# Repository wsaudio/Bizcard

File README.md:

# Bizcard
Drum machine business card: STM32F030 Based drum machine with 4 sounds and 16 pads

FOLDERS
Hardware:
	- Schematics: PDF of schematics
	- Gerbers: Gerber and drill files required for manufacturer
	- Project Files: KiCad V4.0.0 (or later) required to open
	- BOM: Bill of materials required for manufacture
Software: Created with Keil uVision 5.0

Pins configuration:
PA7: Audio output (TIM1 PWM1)
PA0, PA1, PA2, PA3, PA4: LED/Button MUX Out
PA5, PA6, PA9, PA10: LED MUX In
PA13, PA14, PF0, PF1: Button MUX In

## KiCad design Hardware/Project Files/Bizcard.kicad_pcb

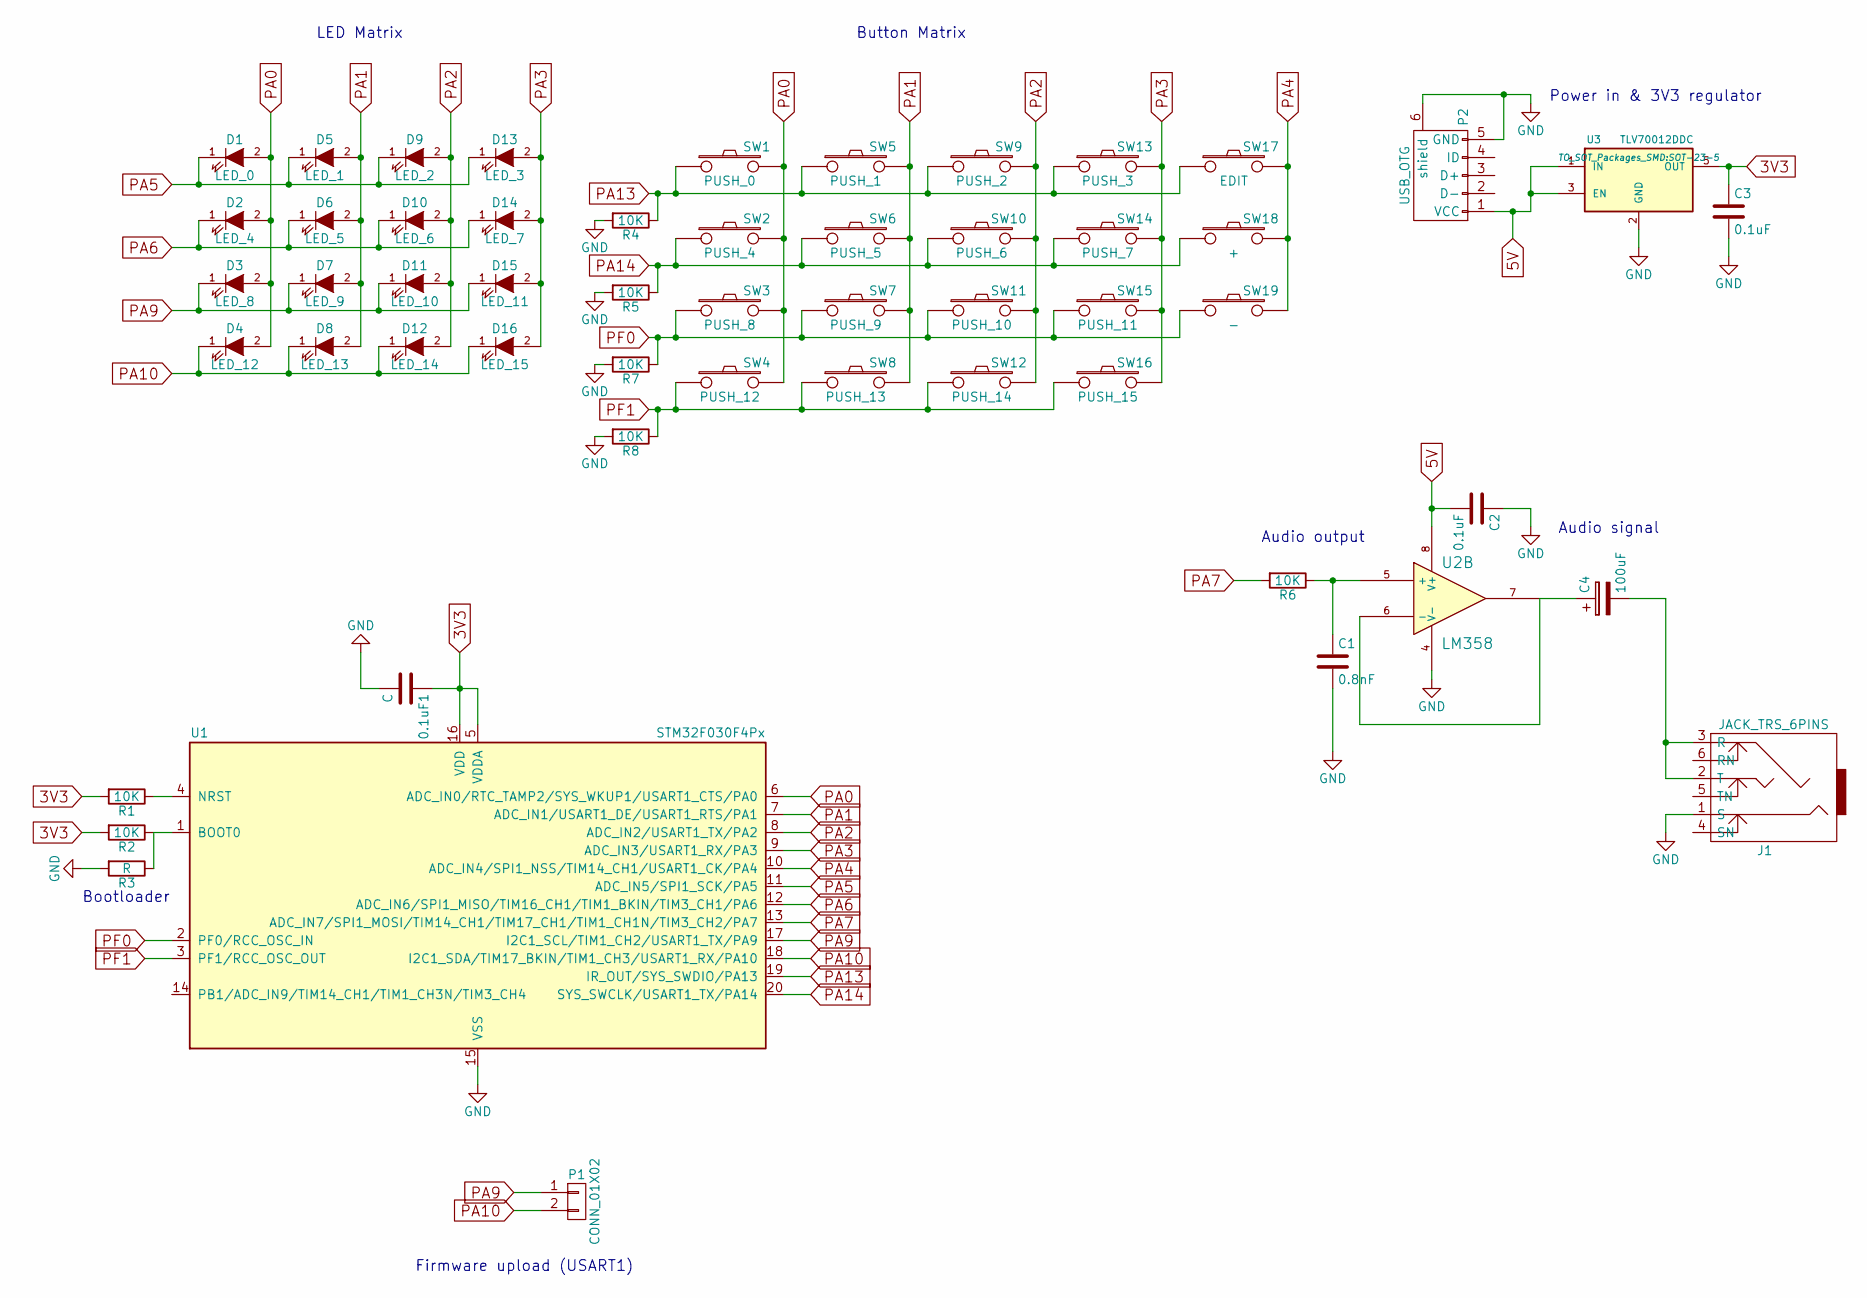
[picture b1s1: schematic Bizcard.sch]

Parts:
0.1uF1: C; C_0402
C1: 0.8nF; C_0402
C2, C3: 0.1uF; C_0402
C4: 100uF; CP_Elec_6.3x4.5
D1: LED_0; LED_0603
D2: LED_4; LED_0603
D3: LED_8; LED_0603
D4: LED_12; LED_0603
D5: LED_1; LED_0603
D6: LED_5; LED_0603
D7: LED_9; LED_0603
D8: LED_13; LED_0603
D9: LED_2; LED_0603
D10: LED_6; LED_0603
D11: LED_10; LED_0603
D12: LED_14; LED_0603
D13: LED_3; LED_0603
D14: LED_7; LED_0603
D15: LED_11; LED_0603
D16: LED_15; LED_0603
J1: JACK_TRS_6PINS; Tayda_3.5mm_stereo_TRS_jack_A-853
P1: CONN_01X02; Pin_Header_Straight_1x02_Pitch2.00mm
P2: USB_OTG; USB_Micro-B_Wuerth-629105150521
R1, R2, R4, R5, R6, R7, R8: 10K; R_0402
R3: R; R_0402
SW1: PUSH_0; SW_PUSH_6mm
SW2: PUSH_4; SW_PUSH_6mm
SW3: PUSH_8; SW_PUSH_6mm
SW4: PUSH_12; SW_PUSH_6mm
SW5: PUSH_1; SW_PUSH_6mm
SW6: PUSH_5; SW_PUSH_6mm
SW7: PUSH_9; SW_PUSH_6mm
SW8: PUSH_13; SW_PUSH_6mm
SW9: PUSH_2; SW_PUSH_6mm
SW10: PUSH_6; SW_PUSH_6mm
SW11: PUSH_10; SW_PUSH_6mm
SW12: PUSH_14; SW_PUSH_6mm
SW13: PUSH_3; SW_PUSH_6mm
SW14: PUSH_7; SW_PUSH_6mm
SW15: PUSH_11; SW_PUSH_6mm
SW16: PUSH_15; SW_PUSH_6mm
SW17: EDIT; SW_PUSH_6mm
SW18: +; SW_PUSH_6mm
SW19: -; SW_PUSH_6mm
U1: STM32F030F4Px; TSSOP-20_4.4x6.5mm_Pitch0.65mm
U2: LM358; SOIC-8_3.9x4.9mm_Pitch1.27mm
U3: TLV70012DDC; SOT-23-5

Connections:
3V3: 0.1uF1.1, C3.1, R1.2, R2.2, U1.5 (VDDA), U1.16 (VDD), U3.5 (OUT)
5V: C2.2, P2.1 (VCC), U2.8 (V+), U3.1 (IN), U3.3 (EN)
GND: 0.1uF1.2, C1.2, C2.1, C3.2, J1.1 (S), P2.5 (GND), P2.6 (shield), R3.2, R4.2, R5.2, R7.2, R8.2, U1.15 (VSS), U2.4 (V-), U3.2 (GND)
unnamed: C1.1, R6.1, U2.5 (+)
unnamed: C4.1, U2.6 (-), U2.7
unnamed: C4.2, J1.2 (T), J1.3 (R)
unnamed: R1.1, U1.4 (NRST)
unnamed: R2.1, R3.1, U1.1 (BOOT0)
PA0: D1.2 (A), D2.2 (A), D3.2 (A), D4.2 (A), SW1.2, SW2.2, SW3.2, SW4.2, U1.6 (ADC_IN0/RTC_TAMP2/SYS_WKUP1/USART1_CTS/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)
PA1: D5.2 (A), D6.2 (A), D7.2 (A), D8.2 (A), SW5.2, SW6.2, SW7.2, SW8.2, U1.7 (ADC_IN1/USART1_DE/USART1_RTS/PA1)
PA2: D9.2 (A), D10.2 (A), D11.2 (A), D12.2 (A), SW9.2, SW10.2, SW11.2, SW12.2, U1.8 (ADC_IN2/USART1_TX/PA2)
PA3: D13.2 (A), D14.2 (A), D15.2 (A), D16.2 (A), SW13.2, SW14.2, SW15.2, SW16.2, U1.9 (ADC_IN3/USART1_RX/PA3)
PA4: SW17.2, SW18.2, SW19.2, U1.10 (ADC_IN4/SPI1_NSS/TIM14_CH1/USART1_CK/PA4)
PA5: D1.1 (K), D5.1 (K), D9.1 (K), D13.1 (K), U1.11 (ADC_IN5/SPI1_SCK/PA5)
PA6: D2.1 (K), D6.1 (K), D10.1 (K), D14.1 (K), U1.12 (ADC_IN6/SPI1_MISO/TIM16_CH1/TIM1_BKIN/T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)
PA7: R6.2, U1.13 (ADC_IN7/SPI1_MOSI/TIM14_CH1/TIM17_CH1/T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)
PA9: D3.1 (K), D7.1 (K), D11.1 (K), D15.1 (K), P1.1, U1.17 (I2C1_SCL/TIM1_CH2/USART1_TX/PA9)
PA10: D4.1 (K), D8.1 (K), D12.1 (K), D16.1 (K), P1.2, U1.18 (I2C1_SDA/TIM17_BKIN/TIM1_CH3/USART1_RX/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)
PA13: R4.1, SW1.1, SW5.1, SW9.1, SW13.1, SW17.1, U1.19 (IR_OUT/SYS_SWDIO/PA13)
PA14: R5.1, SW2.1, SW6.1, SW10.1, SW14.1, SW18.1, U1.20 (SYS_SWCLK/USART1_TX/PA14)
PF0: R7.1, SW3.1, SW7.1, SW11.1, SW15.1, SW19.1, U1.2 (PF0/RCC_OSC_IN)
PF1: R8.1, SW4.1, SW8.1, SW12.1, SW16.1, U1.3 (PF1/RCC_OSC_OUT)

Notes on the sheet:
Firmware upload (USART1)
LED Matrix
Button Matrix
Power in & 3V3 regulator
Audio output
Audio signal
Bootloader

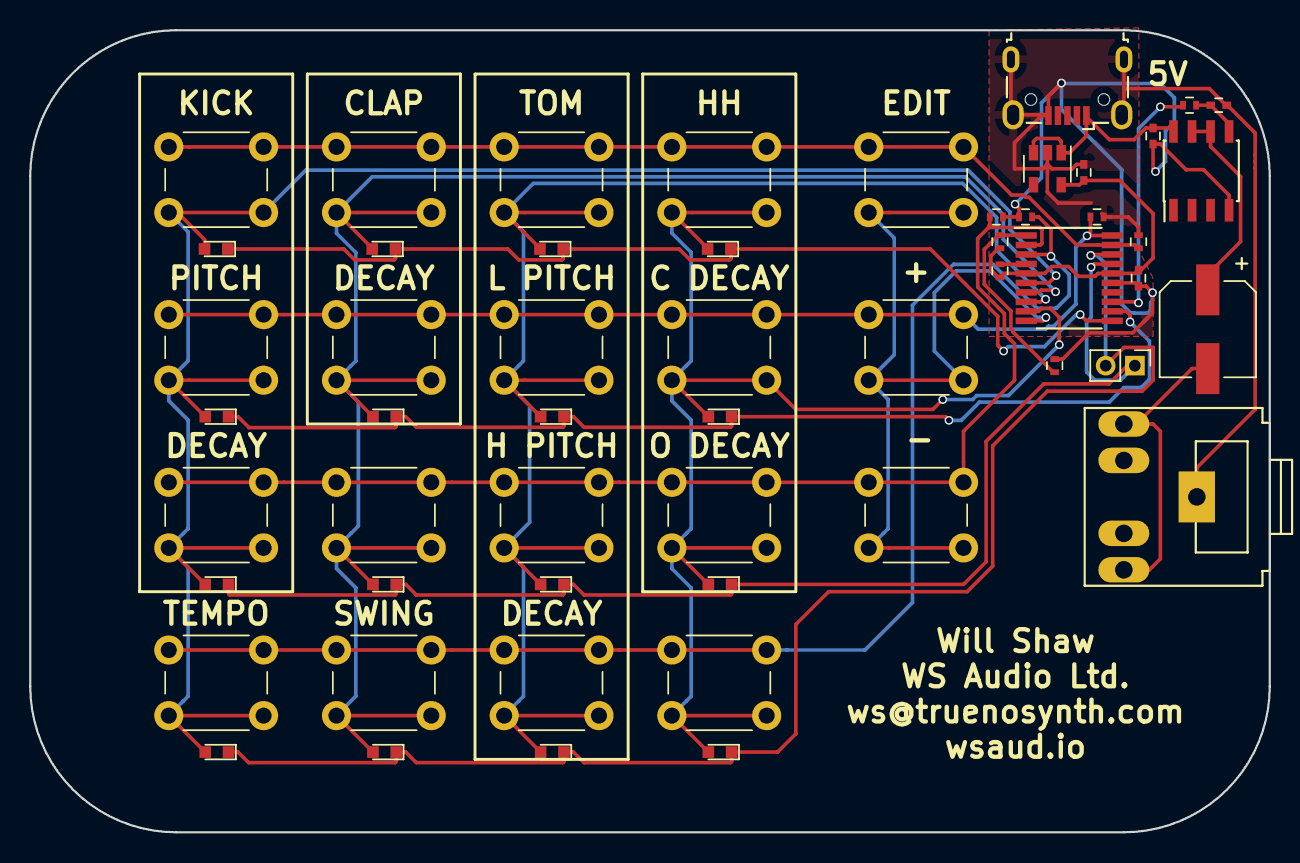
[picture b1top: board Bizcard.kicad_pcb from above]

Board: 2 copper layers, 85.0 x 55.0 mm, 54 parts (0 on the bottom side), 22 nets.

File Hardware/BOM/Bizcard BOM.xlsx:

Reference | Value | Footprint | Notes | Datasheet
C1 | 0.8nF | Capacitors_SMD:C_0402
C2 | 0.1uF | Capacitors_SMD:C_0402
C3 | 0.1uF | Capacitors_SMD:C_0402
C4 | 100uF | Capacitors_SMD:CP_Elec_6.3x4.5 | >= 4V rated
C5 | 0.1uF | Capacitors_SMD:C_0402
D1 | LED_0 | LEDs:LED_0603 | Any 0603 White LED
D10 | LED_6 | LEDs:LED_0603 | Any 0603 White LED
D11 | LED_10 | LEDs:LED_0603 | Any 0603 White LED
D12 | LED_14 | LEDs:LED_0603 | Any 0603 White LED
D13 | LED_3 | LEDs:LED_0603 | Any 0603 White LED
D14 | LED_7 | LEDs:LED_0603 | Any 0603 White LED
D15 | LED_11 | LEDs:LED_0603 | Any 0603 White LED
D16 | LED_15 | LEDs:LED_0603 | Any 0603 White LED
D2 | LED_4 | LEDs:LED_0603 | Any 0603 White LED
D3 | LED_8 | LEDs:LED_0603 | Any 0603 White LED
D4 | LED_12 | LEDs:LED_0603 | Any 0603 White LED
D5 | LED_1 | LEDs:LED_0603 | Any 0603 White LED
D6 | LED_5 | LEDs:LED_0603 | Any 0603 White LED
D7 | LED_9 | LEDs:LED_0603 | Any 0603 White LED
D8 | LED_13 | LEDs:LED_0603 | Any 0603 White LED
D9 | LED_2 | LEDs:LED_0603 | Any 0603 White LED
J1 | JACK_TRS_6PINS | Connectors_USB:Tayda_3.5mm_stereo_TRS_jack_A-853 | Wide style 3.5mm jack
P1 | CONN_01X02 | Pin_Headers:Pin_Header_Straight_1x02_Pitch2.00mm | Not installed - used for programming
P2 | USB_OTG | Connectors_USB:USB_Micro-B_Wuerth-629105150521 | Female micro USB
R1 | 10K | Resistors_SMD:R_0402
R2 | 10K | Resistors_SMD:R_0402
R3 | R | Resistors_SMD:R_0402 | Not installed - used to put in boot mode
R4 | 10K | Resistors_SMD:R_0402
R5 | 10K | Resistors_SMD:R_0402
R6 | 10K | Resistors_SMD:R_0402
R7 | 10K | Resistors_SMD:R_0402
R8 | 10K | Resistors_SMD:R_0402
SW1 | PUSH_0 | Buttons_Switches_ThroughHole:SW_PUSH_6mm | Any 6*6 push button
SW10 | PUSH_6 | Buttons_Switches_ThroughHole:SW_PUSH_6mm | Any 6*6 push button
SW11 | PUSH_10 | Buttons_Switches_ThroughHole:SW_PUSH_6mm | Any 6*6 push button
SW12 | PUSH_14 | Buttons_Switches_ThroughHole:SW_PUSH_6mm | Any 6*6 push button
SW13 | PUSH_3 | Buttons_Switches_ThroughHole:SW_PUSH_6mm | Any 6*6 push button
SW14 | PUSH_7 | Buttons_Switches_ThroughHole:SW_PUSH_6mm | Any 6*6 push button
SW15 | PUSH_11 | Buttons_Switches_ThroughHole:SW_PUSH_6mm | Any 6*6 push button
SW16 | PUSH_15 | Buttons_Switches_ThroughHole:SW_PUSH_6mm | Any 6*6 push button
SW17 | EDIT | Buttons_Switches_ThroughHole:SW_PUSH_6mm | Any 6*6 push button
SW18 | + | Buttons_Switches_ThroughHole:SW_PUSH_6mm | Any 6*6 push button
SW19 | - | Buttons_Switches_ThroughHole:SW_PUSH_6mm | Any 6*6 push button
SW2 | PUSH_4 | Buttons_Switches_ThroughHole:SW_PUSH_6mm | Any 6*6 push button
SW3 | PUSH_8 | Buttons_Switches_ThroughHole:SW_PUSH_6mm | Any 6*6 push button
SW4 | PUSH_12 | Buttons_Switches_ThroughHole:SW_PUSH_6mm | Any 6*6 push button
SW5 | PUSH_1 | Buttons_Switches_ThroughHole:SW_PUSH_6mm | Any 6*6 push button
SW6 | PUSH_5 | Buttons_Switches_ThroughHole:SW_PUSH_6mm | Any 6*6 push button
SW7 | PUSH_9 | Buttons_Switches_ThroughHole:SW_PUSH_6mm | Any 6*6 push button
SW8 | PUSH_13 | Buttons_Switches_ThroughHole:SW_PUSH_6mm | Any 6*6 push button
SW9 | PUSH_2 | Buttons_Switches_ThroughHole:SW_PUSH_6mm | Any 6*6 push button
U1 | STM32F030F4Px | Housings_SSOP:TSSOP-20_4.4x6.5mm_Pitch0.65mm |  | http://www.st.com/content/ccc/resource/technical/document/da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
U2 | LM358 | Housings_SOIC:SOIC-8_3.9x4.9mm_Pitch1.27mm |  | http://www.st.com/content/ccc/resource/technical/document/da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
U3 | TLV70012DDC | TO_SOT_Packages_SMD:SOT-23-5 |  | http://www.farnell.com/datasheets/2108564.pdf?_ga=2.1061687.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

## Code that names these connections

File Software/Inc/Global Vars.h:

/*
STM32F030 Based drum machine

Peripheral configuration:
TIM1: Audio buffer generation, up counter 1024 * 256 (183.1Hz)
TIM3: LED/Button Cycle, up counter to 48000 (1kHz)
TIM14: Audio output PWM, up counter to 1024 (187.5kHz)

Pins configuration:
PA7: Audio output (TIM1 PWM1)
PA0, PA1, PA2, PA3, PA4: LED/Button MUX Out
PA5, PA6, PA9, PA10: LED MUX In
PA13, PA14, PF0, PF1: Button MUX In
*/

#ifndef GLOBAL_VARS
#define GLOBAL_VARS

//Audio
#define fs 23437.5
#define outputBufferSize 512
#define samplesPerChunk 256

//Fixed point conversion
#define fixedPointPos 20
#define fp(x) ((x) << fixedPointPos) //Convert to fixed point
#define ufp(x) ((x) >> fixedPointPos) //Convert to integer

//Ranges ---------------------------------------
//Master Audio
#define volumeSteps 8
//Sequencer
#define tempoMin 20
#define tempoMax 220
#define swingMin 0
#define swingMax 7
//Kick
#define kickPitchMin - 24
#define kickPitchMax 24
#define kickDecMin 1
#define kickDecMax 10
//Clap
#define clapDecMin 1
#define clapDecMax 10
//Toms
#define tomPitchMin - 24
#define tomPitchMax 24
#define tomDecMin 1
#define tomDecMax 10
//HH
#define hhClosedMin 1
#define hhClosedMax 10
#define hhOpenMin 1
#define hhOpenMax 10

//Defaults--------------------------------------
//Master Audio
#define defaultVol 8
#define readPointerDefault 384
#define writePointerDefault 0
//Sequencer
#define defaultTempo 90
#define defaultSwing 0
//Kick
#define defaultKickPitchOffset 0
#define defaultKickDecay 5
//Clap
#define defaultClapDecay 5
//Tom
#define defaultTomPitchOffset 0
#define defaultTomDecay 5
//HH
#define defaultHHCloseDecay 5
#define defaultHHOpenDecay 5

//Generators
#define noOfGenerators 6
#define kickNo 0
#define clapNo 1
#define tomNo 2
#define hhNo 3

//Registers
#define tim1Pwm1CCR (uint32_t*)0x40002034

#endif

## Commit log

2018-03-22 Added hardware, software and readme files
